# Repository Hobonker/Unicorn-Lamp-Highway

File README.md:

# Unicorn-Lamp-Highway

# Inspiration
I'm going to a boarding school so I need stuff for my dorm there. The mascot of the school is unicorns so I decided to try my best shot at a unicorn lamp since I needed a lamp. I want cool stuff in my room.

# What is it?
I mean... it's in the name. It's a lamp in the shape of a unicorn what else could it be

# Materials
3D Printed Unicorn Head

3D Printed Unicorn Body

XIAO RP2040

SK6812 LED Mini x8

Batteries

Wires

USB C to Wall Cable

PCB

Switch

Screws

# Table
### Bill of Materials

| Item                     | Quantity | Link                                                                    | Price |
|--------------------------|----------|-------------------------------------------------------------------------|-------|
| Seeed Studio XIAO RP2040 | 1        | [Amazon](https://www.amazon.com/dp/B09NNVNW7M)                          | $10   |
| SK6812 Mini RGB LEDs     | 8        | N/A I already have                                                      | $0    |
| USB C to Wall Cable      | 1        | https://www.amazon.com/USB-C-Wall-Fast-Charger/dp/B0CF5CLMVV?gQT=1      | $5    |
| Jumper Wires (M-M)       | Assorted | N/A I already have                                                      | $0    |
| USB-C Cable              | 1        | N/A I already have                                                      | $0    |
| Superglue or Hot Glue    | 1        | N/A I already have                                                      | $0    |
| Breadboard               | 1        | N/A I already have                                                      | $0    |
| PCB                      | 5        | JLC PCB                                                                 | $25   |
| Switch                   | 1        | N/A I already have                                                      | $0    |
| Screws                   | 2        | N/A I already have                                                      | $0    |

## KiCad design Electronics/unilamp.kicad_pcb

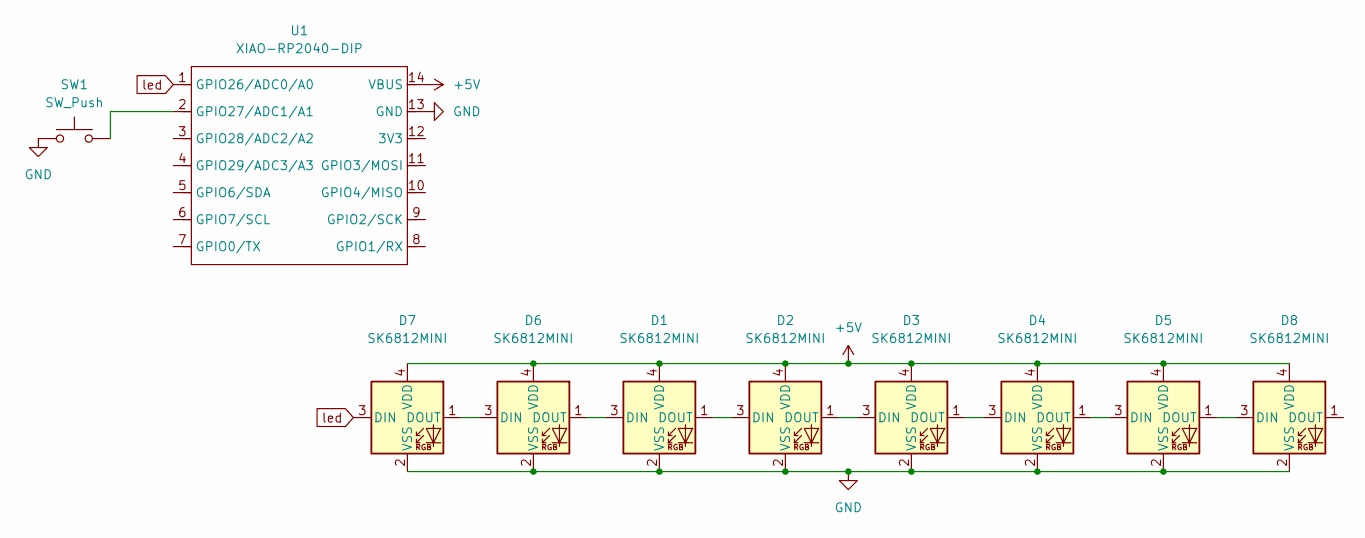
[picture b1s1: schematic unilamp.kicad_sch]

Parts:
D1, D2, D3, D4, D5, D6, D7, D8: SK6812MINI; LED_SK6812MINI_PLCC4_3.5x3.5mm_P1.75mm
SW1: SW_Push; SW_Cherry_MX_1.00u_PCB
U1: XIAO-RP2040-DIP

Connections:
+5V: D1.4 (VDD), D2.4 (VDD), D3.4 (VDD), D4.4 (VDD), D5.4 (VDD), D6.4 (VDD), D7.4 (VDD), D8.4 (VDD), U1.14 (VBUS)
GND: D1.2 (VSS), D2.2 (VSS), D3.2 (VSS), D4.2 (VSS), D5.2 (VSS), D6.2 (VSS), D7.2 (VSS), D8.2 (VSS), SW1.1, U1.13 (GND)
unnamed: D1.3 (DIN), D6.1 (DOUT)
unnamed: D1.1 (DOUT), D2.3 (DIN)
unnamed: D2.1 (DOUT), D3.3 (DIN)
unnamed: D3.1 (DOUT), D4.3 (DIN)
unnamed: D4.1 (DOUT), D5.3 (DIN)
unnamed: D5.1 (DOUT), D8.3 (DIN)
unnamed: D6.3 (DIN), D7.1 (DOUT)
unnamed: SW1.2, U1.2 (GPIO27/ADC1/A1)
led: D7.3 (DIN), U1.1 (GPIO26/ADC0/A0)

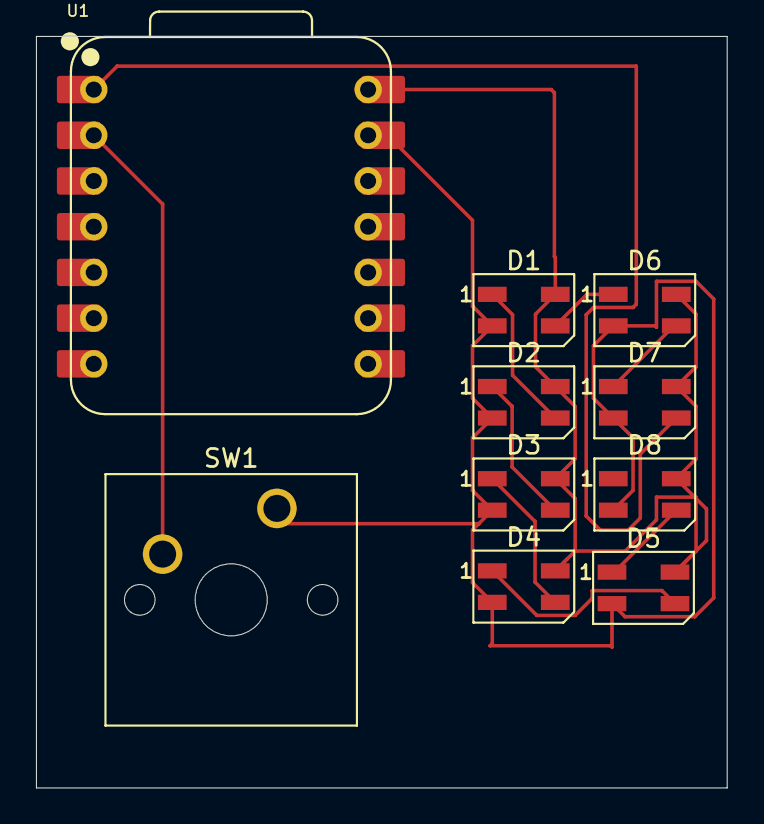
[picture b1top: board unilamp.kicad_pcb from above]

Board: 2 copper layers, 38.4 x 41.8 mm, 10 parts (0 on the bottom side), 11 nets.

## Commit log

2025-07-29 Rename Unicorn Lamp Body.step to Cad Files/Unicorn Lamp Body.step
2025-07-29 Rename Unicorn Lamp Head.step to Cad Files/Unicorn Lamp Head.step
2025-07-29 Rename Cad Files/JOURNAL.md to JOURNAL.md
2025-07-29 Rename Lamp Head.png to Images/Lamp Head.png
2025-07-29 Rename Lamp Torso.png to Images/Lamp Torso.png
2025-07-29 Rename Torso Bottom.png to Images/Torso Bottom.png
2025-07-29 Rename unicornlampbody.png to Images/unicornlampbody.png
2025-07-29 Rename main.py to Firmware/main.py
2025-07-29 Rename main.py to main.py
2025-07-29 Rename Unicorn Body.step to CAD/Unicorn Body.step
2025-07-29 Rename Unicorn Head.step to CAD/Unicorn Head.step
2025-08-05 Rename Fully Assembled Unicorn Lamp No Space.step to Connected Fully Assembled Unicorn Lamp.step
